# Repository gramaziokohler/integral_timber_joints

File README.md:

# integral_timber_joints

Python library for designing timber structures with integral timber joints.

This repo is part of the [Robotic Assembled Timber Structures with Integral Timber Joints](https://github.com/gramaziokohler/integral_timber_joints) project.

## Design Goals

The goal of the python library is to be able to achieve the following high-level functions:

- Classes and Data Structure for describing:
  - Timber elements
  - Integral joints (Subtractive machining joint)
  - Process tools (Grippers, Clamps, Pickup Station)
  - Process action (Actions and Movements)
- Algorithms for assembly design
  - Creating beams from Rhino geometry
  - Creating joint pairs from beam intersection
- Algorithms for process design
  - Computing assembly process information (assembly sequence, gripper type, clamp type, grasp pose, clamp attachment pose)
    - From user input as guide
    - Automatic deduction (Auto Sequence, Auto Lap Joint Direction)
  - Computing robotic movements
    - Key positions
    - Robotic Path (Path Planning)

## Installation (library)

### Conda environment (optional)

Create a new environment with python 3.7 and install this package in the new environment

```bash
conda create --name itj python=3.7
conda activate itj
```

One of the dependency from `compas` is planarity, which depends of `cython`. You will need to install this manually:

```bash
pip install cython --install-option="--no-cython-compile"
```

or

```bash
conda install cython
```

### Clone and update submodules

Install this library from source by cloning this repo to local and install from source.

```bash
git clone --recursive https://github.com/gramaziokohler/integral_timber_joints.git
cd integral_timber_joints
```

The `--recursive` flag when cloning above is used for initializing all the git submodules. You can learn more about submodules [here](https://git-scm.com/book/en/v2/Git-Tools-Submodules).

Later in the development, whenever you need to update the submodules, issue the following:

```bash
git submodule update --init --recursive
```

### Install libraries

Run this the following in terminal from the root folder of this repo. All libraries are installed from source (in the [editable mode](https://pip.pypa.io/en/stable/reference/pip_install/#install-editable)).

```bash
# Install the submodule libraries from source
pip install -e .\external\compas
pip install -e .\external\compas_fab
pip install -e .\external\compas_fab_pychoreo

# install `integral_timber_joints` from source 
pip install -e .

# Run the following code add the python library paths to Rhino / Grasshopper:
python -m compas_rhino.install -p compas compas_fab compas_ghpython roslibpy compas_rhino jsonpickle integral_timber_joints geometric_blocking
```

<!-- Note that there maybe error message from `pip` indicating version incompatibility of `compas` with `compas_fab`, this is fine.  -->

Alternatively if development is intended you can install with developer tools:

```bash
# replace `pip install -e .` above with
pip install -r requirements-dev.txt
invoke add-to-rhino
```

⚠ when used in rhino, please start the RPC proxy beforehand by: `compas_rpc start`

#### Python dependencies, explained

The following python dependency are installed in the above process. See [requirements.txt](https://github.com/gramaziokohler/integral_timber_joints/blob/master/requirements.txt) for more info on the specific versions pinned.

The following libraries are installed "automatically" (via pip or conda, learn about their difference [here](https://www.anaconda.com/blog/understanding-conda-and-pip#:~:text=Pip%20installs%20Python%20packages%20whereas,software%20written%20in%20any%20language.&text=Another%20key%20difference%20between%20the,the%20packages%20installed%20in%20them.))
- `compas` (Library for geometrical modeling and graph relationship)
- `compas_fab` (Library for modelling Tools and Robots, functions to call ROS backend for path planning)
- `jsonpickle` (Serialization library for Tools, Assembly, Process)
- `trimesh` (Call Openscad in the background to perform Mesh Boolean)
- `pycddlib` (Computation of blocking direction analysis)
- `CGAL` (SWIG bindings for remeshing operations)

The CGAL bindings are best installed from conda: `conda install -c conda-forge cgal`. Otherwise, you have to be brave enough to build from source following instructions [here](https://github.com/CGAL/cgal-swig-bindings/wiki/Installation).

The following two libraries are installed manually from git submodules, to better keep track of our development cycles:
- `pybullet_planning` (Library for planning utilities in pybullet)
- `compas_fab_pychoreo` (Library for providing `pybullet_planning` functionalities through a `compas_fab`-friendly API)

## Installation (external software dependency)

Install the following software:

- Rhino V6 (Design interface for demo file)
- Grasshopper plugin
  - [Elefront](https://www.food4rhino.com/app/elefront) (Handles clickable mesh interface)

- [Openscad](https://www.openscad.org/downloads.html) (This will be running in the background. Start the software at least once after installing)

## Module Structure

See [this markdown file](src/Module_Structure.md) regarding the organization of the code and how it relates to dependency and `compas` core libraries.

## Sequence and Motion Planning

See [this file](./planning_instructions.md) for instructions on running the planning.

Credits
-------------

This repository was created by Pok Yin Victor Leung (<leung@arch.ethz.ch>) [@yck011522](https://github.com/yck011522) at [@gramaziokohler](https://github.com/gramaziokohler), with the help of other [contributors](https://github.com/gramaziokohler/integral_timber_joints/blob/master/AUTHORS.rst).

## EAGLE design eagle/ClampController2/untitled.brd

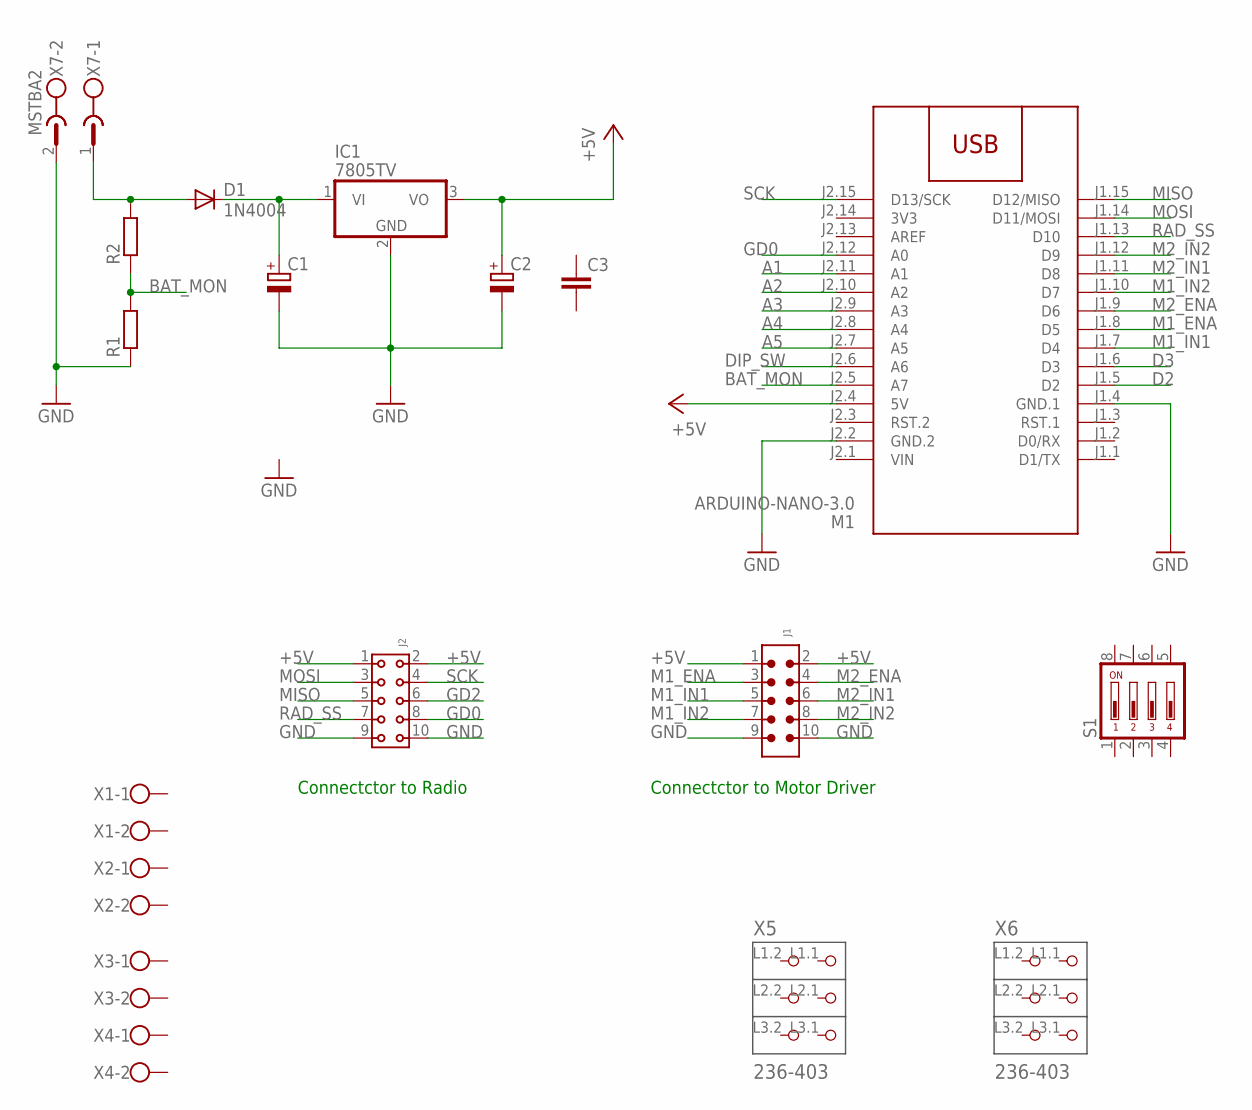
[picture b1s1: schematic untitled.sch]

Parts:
C1, C2: CPOL-EUE10-20; EB20D
C3: C-EU050-030X075; C050-030X075
D1: 1N4004; DO41-10
IC1: 7805TV; TO220V
J1: 6120XX21621_61201021621; 61201021621
J2: 6130XX21821_61301021821; 61301021821
M1: ARDUINO-NANO-3.0
R1, R2: R-EU_0207/7; 0207/7
S1: DIP04YL
X1, X2, X3, X4: W237-102
X5, X6: 236-403; P-236-403
X7: MSTBA2

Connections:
3V3: M1.J2.14 (3V3)
+5V: C2.+, IC1.3 (VO), J1.1, J1.2, J2.1, J2.2, M1.J2.4 (5V)
A1: M1.J2.11 (A1)
A2: M1.J2.10 (A2)
A3: M1.J2.9 (A3)
A4: M1.J2.8 (A4)
A5: M1.J2.7 (A5)
BAT_MON: M1.J2.5 (A7), R1.2, R2.1
D2: M1.J1.5 (D2)
D3: M1.J1.6 (D3)
DIP_SW: M1.J2.6 (A6)
GD0: J2.8, M1.J2.12 (A0)
GD2: J2.6
GND: C1.-, C2.-, IC1.2 (GND), J1.9, J1.10, J2.9, J2.10, M1.J1.4 (GND.1), M1.J2.2 (GND.2), R1.1, X7.2
M1_ENA: J1.3, M1.J1.8 (D5)
M1_IN1: J1.5, M1.J1.7 (D4)
M1_IN2: J1.7, M1.J1.10 (D7)
M2_ENA: J1.4, M1.J1.9 (D6)
M2_IN1: J1.6, M1.J1.11 (D8)
M2_IN2: J1.8, M1.J1.12 (D9)
MISO: J2.5, M1.J1.15 (D12/MISO)
MOSI: J2.3, M1.J1.14 (D11/MOSI)
unnamed: D1.A, R2.2, X7.1
unnamed: C1.+, D1.C, IC1.1 (VI)
RAD_SS: J2.7, M1.J1.13 (D10)
SCK: J2.4, M1.J2.15 (D13/SCK)
VIN: M1.J2.1 (VIN)

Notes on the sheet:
Connectctor to Motor Driver
Connectctor to Radio

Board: 2 copper layers, 18 parts (0 on the bottom side), 16 nets, no tracks yet.

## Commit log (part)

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2021-09-16 Design repo update with Nine Pieces Planned Result - Also a Symbolic planning nine_piece
2021-09-16 fix small bud in ui delete tools
2021-09-17 NP Joint change thickness
2021-09-17 WIP Better algorithm to convert Brep to Beam Frame Fixes #101
2021-09-18 GH File used to interactively figure out the new algorithm
2021-09-18 Design Study update with new setting out
2021-09-23 Add BeamcutFourCorners class. Fixes #105
2021-09-23 fix #98
2021-09-23 Fix joints error for the beam depth 139
2021-09-23 Cacheing Draw State for faster UI performance - Added __eq__ to ObjectState - Added `state_visualization_current_state` to ProcessArtist ` ProcessArtist._get_state_attached_objects_meshes now takes `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
2021-09-23 Fix #99
2021-09-24 Fix Wrong pickup rotation for beam with 1 screwdriver #108
2021-09-24 Fix mistake in `compute_beam_pickupretract` not setting `assembly_wcf_pickupretract`
2021-09-24 Refactored GripperAlignedPickupStation to allow different pickup frame and config for different tools. Fix #62
2021-09-27 Add Gripper and Screw Report. Fix #90
2021-09-27 Updated Nine Piece Screwdriver pickup position
2021-09-27 Hot fix for #112
2021-09-28 Fix #112
2021-09-28 Add logging to file to run.py, exposed `solve_timeout` parameter
2021-09-28 ad-hoc attempt for #110
2021-09-29 Fix #113 `assembly.transtform` function
2021-09-29 run.py expose rrt_iterations and reachable_range
2021-09-30 Attempt #107
2021-10-01 Fix #107, Fix #100
2021-10-01 Adding Polyline Joint definition
2021-10-01 compas_triangle requirement
2021-10-04 changed box implementation to polyhedron_extrude_from_concave_vertices
2021-10-04 ui for changing joint_type
2021-10-04 JointPolylineLap Angle properity
2021-10-04 more verbose
2021-10-04 compute_states_verbose
2021-10-04 Improved Rhino Assembly Artist with MergeCoplanarFaces
2021-10-05 ui to _change_joint_polyline_lap_string
2021-10-05 mesh_weld is evil. no mesh_weld
2021-10-05 Iterative Boolean Union
2021-10-05 JointPolylineLap thickness parameter
2021-10-05 changing PolylineLap thickness
2021-10-05 Nine piece have Polyline Joints
2021-10-05 Improve Joint selection UI
2021-10-05 Hypar Test Plan Round 2 Results
2021-10-06 multi select
2021-10-06 Model BeamAssemblyMethod.GroundContact for Nine Piece
2021-10-06 pddlstream problem construction
2021-10-06 solver struggles to find a solution for the simplest problem
2021-10-07 fix temp IK not drawing properly
2021-10-07 clamp-free symbolic plan working
2021-10-07 80% #66, Symbolic planning works fully for nine-pieces without screw drivers, haven't visualize it though
2021-10-10 fix bug in _change_joint_non_planar_lap_beam_stay_face_id
2021-10-10 trim preset at 600 mm
2021-10-11 Polyline encoder with a few more options
2021-10-12 Fix #129 - Added polyline Joint and Angle visualization to polyline Encoder
2021-10-12 Bug Fix
2021-10-12 Scaffording added to Nine Piece Design
2021-10-12 start plan viz
2021-10-13 Hyparhut design update
2021-10-14 consider_transition flag in pddl construction
2021-10-18 Fix #122
2021-10-20 Polyline encoder update
2021-10-21 attempt to get rid of some cyclic import
2021-10-21 Fix #128 Beam Endcut for Plate Slot
2021-10-21 encoder update
2021-10-27 Add Brep and Mesh Acute angle Checking tool. Fix #137
2021-10-27 Fixed NP joints <90 problem Fix #136
2021-10-29 Add one dowel to the boolean geometry
2021-11-01 use pyplanner for fluent-problem
2021-11-02 debug symbolic domain for Caelan
2021-11-02 file renaming
2021-11-03 Fix error in assembly.joint_ids returning them in wrong sequence
2021-11-04 gripper_report is now tool_report, contain clamp info
2021-11-04 symbolic plan works after IK reform
2021-11-04 better camera pos
2021-11-04 use conditional effect to simplify pick_tool
2021-11-08 Better Loggin message, Debug logging only in debug mode.
2021-11-09 adaptive alg works, Derived or fix
2021-11-10 design study update
2021-11-11 pyplanner derived precondition bug
2021-11-12 Half-baked prototype of including IK into pddlstream
    Related to #134
2021-11-24 modifying env_model trigger action invalidation
2021-11-24 change some verbosity
2021-11-24 Script to export brep withour screwdriver holes. Fix #139
2021-11-24 Script to load joint customization into polyline joints
2021-12-14 remove pddlstream submodule
2021-12-14 Design study updates
2021-12-16 symbolic plan viz in Rhino
2022-01-05 Changed some Movement tags
2022-01-05 New PDDL parse function
2022-01-05 pddlstream plan to process fn
2022-01-07 ITJ_ACTION_CLASS_FROM_PDDL_ACTION_NAME
2022-01-07 Export process
2022-01-07 latest design study file update
2022-01-11 pp log
2022-01-15 Use a derived predicate to force dummy actions to set screwdrivers in pose
2022-01-17 before splitting tool to/from rack actions
2022-01-17 Split tool from rack actions
2022-01-17 Bundled screwdriver action works great
2022-01-18 PG Grippers CM updated - CM now bigger
2022-01-20 stream predicates
2022-01-21 PG1500 Base Plate updated and thus model change.
2022-01-22 Perform FK to get frame when setting taught config Design Repo UPdated
2022-01-22 planned result FK mismatch problem diagnose tool
2022-01-24 Rhino UI Visualize Trajectory should use FK for displaying attached tools Fixes #142
2022-01-24 Fix state bugs
2022-01-26 Debug files trying to understand problem #144 #155
2022-01-26 Fix bug for incorrectly calling FK on non RoboticMovement when painting Robot
2022-01-26 rfl_description repo updated after dance
2022-01-28 submodule updates
2022-01-28 WIP tolerance clean up
2022-01-28 run.py documentation
2022-01-31 clean up frame and conf comparison
2022-02-01 update itj_design_study
2022-02-01 Fix set_state options passing in compute_linear free motion
2022-02-01 Fix ACM error in `RetractScrewdriverFromBeamAction`
2022-02-01 Hyparhut Process file update.
2022-02-03 load_external_movements now auto attempt to load smoothed movements
2022-02-03 removed a print statement
2022-02-03 tqdm progress bar and no_smooth
2022-02-08 archive movement jsons
2022-02-08 speed_type='speed.assembly.screw_retract'
2022-02-08 Two-way movement file move, restart solve without restarting client
2022-02-09 separate save process and movements
2022-02-09 Fix AcquireDockingOffset having incorrect init with extra comma
2022-02-10 skip saving non-robotic movement
2022-02-10 Parametric `get_movement_start_robot_config` and `_end_` to skip NonRoboticMovements Fixes #150
2022-02-11 clean up check_state msg
2022-02-11 more check states printout cleanup
2022-02-12 wrt #150, get rid of prop_state and update process loading mechanism for restarts
    Move collision_distance_threshold into robot_setup.py to make sure run.py and check_states.py are using the same tolerance setup
2022-02-13 Pin compas_triangle==1.0.2
2022-02-18 design_study process update after `planning_linear_step_distance_m`
2022-02-18 small cleanup
2022-02-21 use_stored_seed test
2022-02-21 submodule update
2022-02-21 Changed API for Start End Config Problem Fixes #153
2022-02-22 use_stored_seed flag
2022-02-22 Remove redundant process loading from json in restart
2022-02-25 Add ClampsJawMovement with `allowable_target_deviation`
2022-02-25 What.py outline
2022-02-25 Process file update after new screwdriver movement
2022-02-27 fix tool conf in sweep_collision_check and speedup verify traj
2022-03-01 Fix typo in ScrewdriverMovement
2022-03-01 Changed speed setting for the further away storage linear approach and retract
2022-03-02 Added more mesh points to Screwdrivers and increase approach / retraction distance.
2022-03-02 Hyparhut process file updated. Multiple changes to env, ClampModel, ScrewdriverModel, Planning Skeleton.
2022-03-02 all_conf_close print fix
2022-03-08 RFL Robot Collision Mesh made bigger
2022-03-11 Fix diagnosis viz bug
2022-03-16 Fix the still incorrect tightening amount
2022-03-16 Pick and Place GripperFromStorageAction no longer moves the gripper jaw.
2022-03-16 Add SetWorkpieceWeight to beam pickup and placement
2022-03-16 Better Tag for SetWorkpieceWeight
2022-03-17 Hot fix to add a intermediate position before beam reorientation.
2022-03-17 rfl description CM bigger
2022-03-21 ad-hoc fix for when planning for reorientation linear movement fails
2022-03-23 stream function WIP
2022-03-30 Rhino UI shortcut to next Free Move Trajectory
2022-03-31 fixing incorrect Z axis limit
2022-04-01 Replanned roof elements
2022-04-01 Larger screwdriver uncertainty. Beam transfer free move higher planning priority
2022-04-05 pick, place_clamp stream sampling working
2022-04-07 Design Files of the as finished HyparHut
2022-04-07 Updated robot model collision model
2022-04-13 fix act_n in postprocessing
2022-04-22 solve serialized incremental
2022-04-28 update itj design study
2022-04-28 typo bug
2022-04-29 Add pddlstream and pyplanners submodule
2022-05-18 Added ui_replace_scaffold_geometry
2022-05-18 cgal split long edges, fix #157
2022-05-18 Add mesh_split_long_edge_max_length to run.py
2022-05-18 Add storageapproach1_vector and storageapproach2_vector for CL3 Clamps
2022-05-18 More convenient while loop for replacing multiple tools
2022-05-19 Modified PickClampFromStorageAction and PlaceClampToStorageAction to use storageapproach1(&2)_vector
2022-05-21 Added Docking Movement to PickClampFromStructureAction and PlaceClampToStructureAction
2022-05-21 Added traj purge before saving process from Rhino
2022-05-21 Added test movement in CantiBoxRight A235_M0 for intermediate waypoint
2022-05-21 Fix Rhino Visualize Traj not loading rough traj
2022-05-22 Improve edbug message
2022-05-22 Added `SOLVE_MODE.linear_motion_only`
2022-05-22 fixed warn to warning
2022-05-22 Add automatic removal of neighbouring overconstraining Free Movement
2022-05-24 WIP Linear Movement Group
2022-05-25 WIP run_global, linear group planning works
2022-05-25 Fix bug in solving for linear_movement_group in run.py
2022-05-25 run_global first pass
2022-05-25 run_global print patches
2022-05-26 Refactor visualize trajectory, preparing for interactive slider
2022-05-26 Add Trajectory Slider in Visualize Trajectory
2022-05-26 bug fix in run_global.py
2022-05-26 Planning instruction update
2022-05-26 Failed movements ids are printed as CSV without spacing
2022-05-26 Multiple movement_id support in run_global and refactored code.
2022-06-02 Add dense sampled sweep collision check to check_states
2022-06-04 Improved sequence report for production list
2022-06-04 Design Repo before PDDL Planning Canti Left and Mid
2022-06-05 Changed clamp_appraoch_position to 230mm
2022-06-05 Changed some Movements in Actions after lessons from CantiRight - Added CancelRobotOffset to all *ToStorage Actions - Removed one `operator_stop_before` in `PlaceClampToStructureAction` - Added one o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
2022-06-05 bug in run_blobal
2022-06-05 -keep optioned by LMG replanning not killing neighboring FMs
2022-06-06 Add support for screwed without gripper element
    Add xyz gantry rejection in gantry sampling function
2022-06-06 Fix redundant screwdriver removal in PDDL plan conversion
2022-06-06 RFL Robot CM bigger again
2022-06-06 Better debug message for check_state
2022-06-07 prev_action for screwed element's stream fn
    Add support for beam_placement_without_clamp
2022-06-08 Supports for all beam placement done and tested on all three boxes.
2022-06-08 Support for multiple movement_ids separated by a comma in check_states
2022-06-10 Design Update. Beginning of CantiMid Production
2023-05-19 Some screen captures
2023-09-29 Consolidated submodule updates.
2023-09-29 from compas.data import DataDecoder, DataEncoder
2023-09-29 function to load pddl result from json
2023-10-03 compas_fab use robarch_pddl branch
2023-10-03 Fixed a tab error in Rhino.load_tamp_results
2023-10-03 Visualize movement iterates through all beams even if the beam is not in sequence
2023-10-03 Adding and visualizing TAMP trajectory
2023-10-08 Removed submodule external/abb_irb4600_40_255
2023-10-11 parse clamp trajectory from TAMP results
2023-10-11 Trajectory is working

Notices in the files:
parts and their libraries:
Wurth_Connectors_WR-BHD: Copyright: Würth Elektronik
diy-modules: Released under the Creative Commons Attribution 4.0 International License: http://creativecommons.org/licenses/by/4.0
